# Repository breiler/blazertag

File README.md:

# blazertag
A laser tag game using Arduino and IR sensor

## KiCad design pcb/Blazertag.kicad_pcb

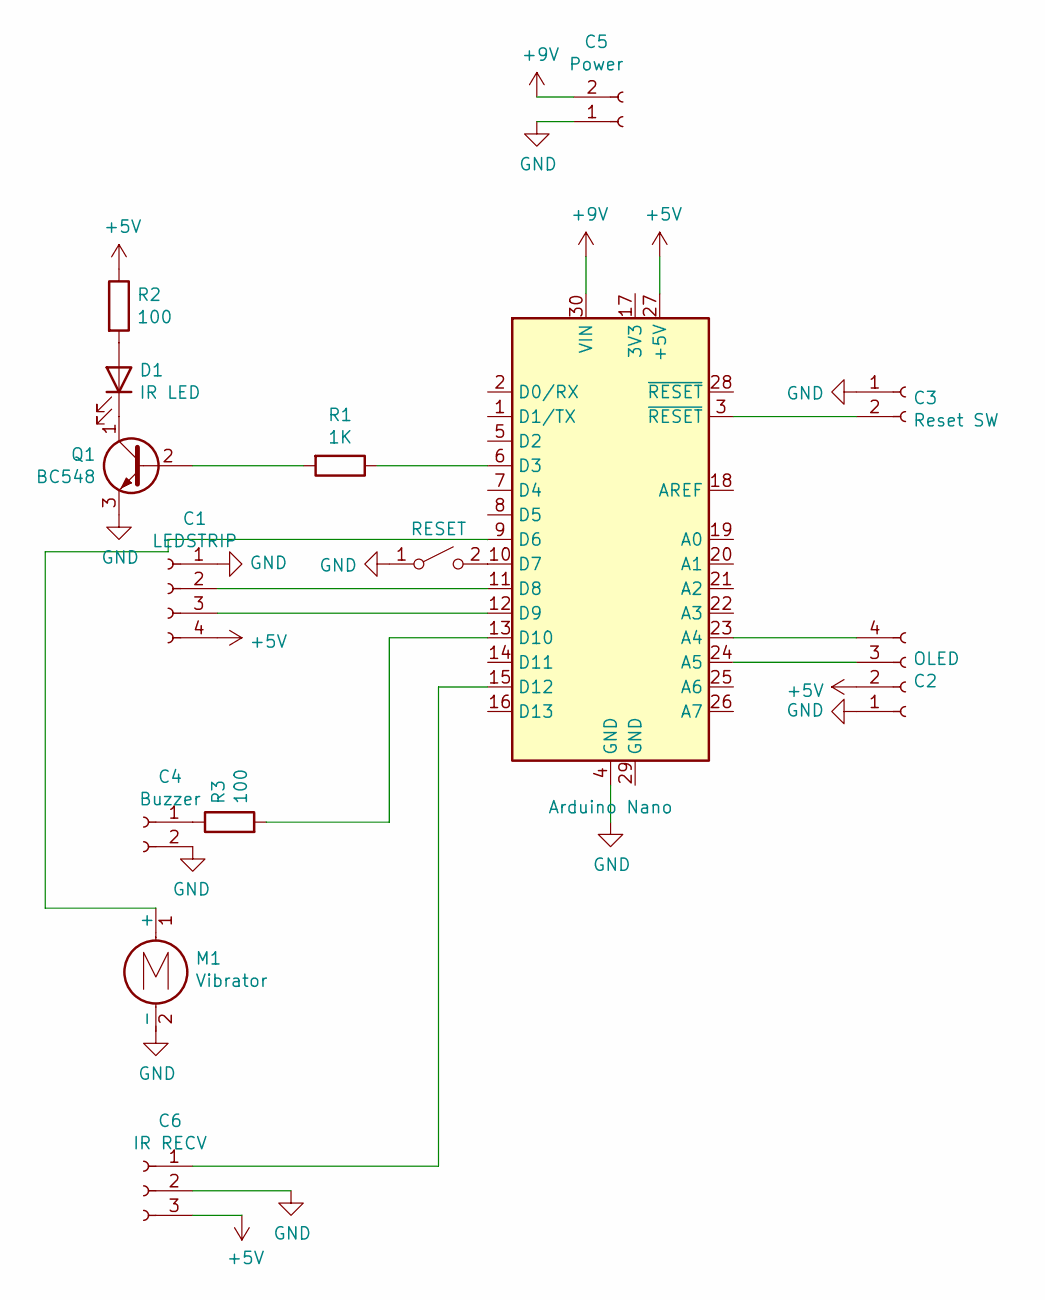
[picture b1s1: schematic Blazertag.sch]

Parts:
A1: Arduino Nano; Arduino_Nano
C1: LEDSTRIP; PinHeader_1x04_P2.54mm_Vertical
C2: OLED; PinHeader_1x04_P2.54mm_Vertical
C3: Reset SW; PinHeader_1x02_P2.54mm_Vertical
C4: Buzzer; Buzzer_15x7.5RM7.6
C5: Power; PinHeader_1x02_P2.54mm_Vertical
C6: IR RECV; PinHeader_1x03_P2.54mm_Vertical
D1: IR LED; LED_D5.0mm_IRGrey
M1: Vibrator; PinHeader_1x02_P2.54mm_Vertical
Q1: BC548; TO-92_Wide
R1: 1K; R_Axial_DIN0207_L6.3mm_D2.5mm_P10.16mm_Horizontal
R2, R3: 100; R_Axial_DIN0207_L6.3mm_D2.5mm_P10.16mm_Horizontal
SW1: RESET; PinHeader_1x02_P2.54mm_Vertical

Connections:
+5V: A1.27 (+5V), C1.4, C2.2, C6.3, R2.1
+9V: A1.30 (VIN), C5.2
GND: A1.4 (GND), C1.1, C2.1, C3.1, C4.2, C5.1, C6.2, M1.2 (-), Q1.3 (E), SW1.1 (A)
unnamed: A1.3 (~RESET), C3.2
unnamed: A1.6 (D3), R1.1
unnamed: A1.9 (D6), M1.1 (+)
unnamed: A1.10 (D7), SW1.2 (B)
unnamed: A1.11 (D8), C1.2
unnamed: A1.12 (D9), C1.3
unnamed: A1.13 (D10), R3.2
unnamed: A1.15 (D12), C6.1
unnamed: A1.23 (A4), C2.4
unnamed: A1.24 (A5), C2.3
unnamed: C4.1, R3.1
unnamed: D1.1 (K), Q1.1 (C)
unnamed: D1.2 (A), R2.2
unnamed: Q1.2 (B), R1.2

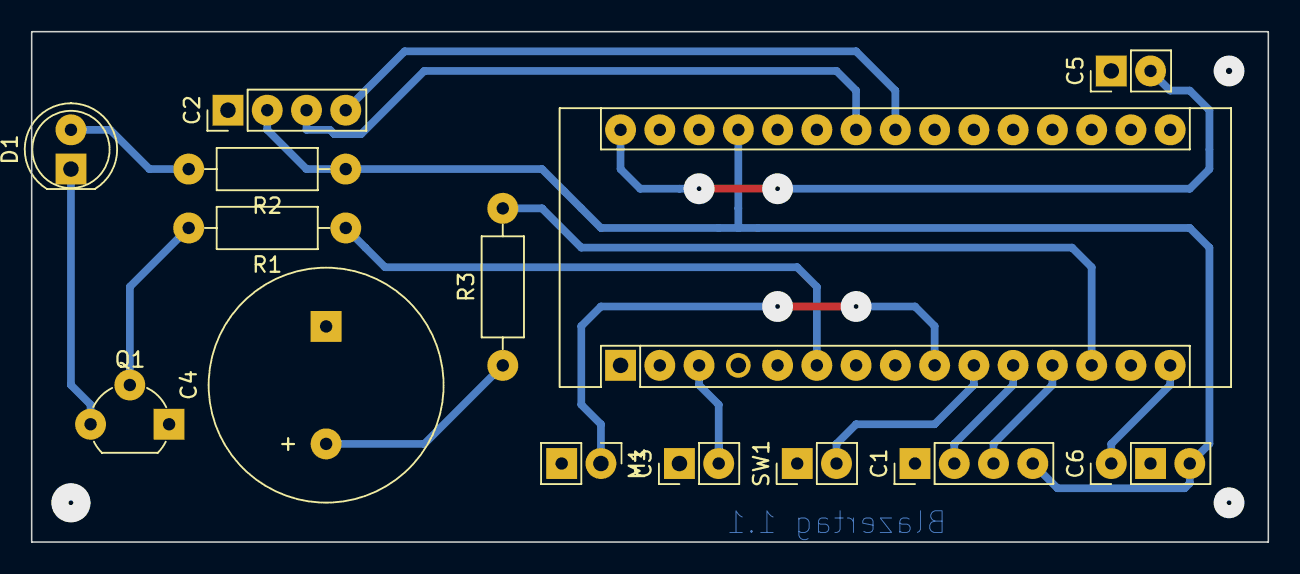
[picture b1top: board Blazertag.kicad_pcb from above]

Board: 2 copper layers, 80.0 x 33.0 mm, 14 parts (0 on the bottom side), 17 nets.

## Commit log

2021-09-27 Initial import
2021-09-27 Minimized the memory footprint
2021-09-27 Removed unused include
2021-09-28 Added support for OLED display and changed colors
2021-09-30 Added IR sender for firing which now transmits the team and player id.
2021-10-06 Added PCB and environment settings for ESP32.
